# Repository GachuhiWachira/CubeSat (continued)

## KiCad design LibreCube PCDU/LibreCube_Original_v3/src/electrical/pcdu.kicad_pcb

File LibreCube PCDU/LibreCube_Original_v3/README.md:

# LibreCube / Platform / Power / Power Module

A basic Power Conditioning and Distribution Unit (PCDU) that
implements a full redundancy scheme and adheres to the LibreCube board
specification. The main features are:

- Input connectors for up to six solar cells (in configurations for up to 5 Volt)
- Conditioning of input power (linear energy transfer mode)
- Two Li-Ion batteries integrated on board
- Charge and discharge circuitry for batteries, depending on solar input and load
- Main power switch that disconnects all electrical loads from solar cell input and batteries
- Stable 5 Volt output power to attached loads
- Eight output switches for switchable loads

The user manual can be found [here](docs/manual/README.md).

## How to Build

See [here](docs/assembly/README.md) for instructions.

## How to Modify

The `src` folder contains the [KiCAD](https://www.kicad.org/) source files.

## Contribute

To learn more on how to successfully contribute please read the contributing
information in the [LibreCube Guidelines](https://librecube.gitlab.io/).

Want to get involved? Join us at [Matrix](https://app.element.io/#/room/#librecube.org:matrix.org)
or via [Email](mailto:info@librecube.org).

## License

The project is licensed under the CERN Open Hardware license.
See the [LICENSE](./LICENSE.txt) file for details.

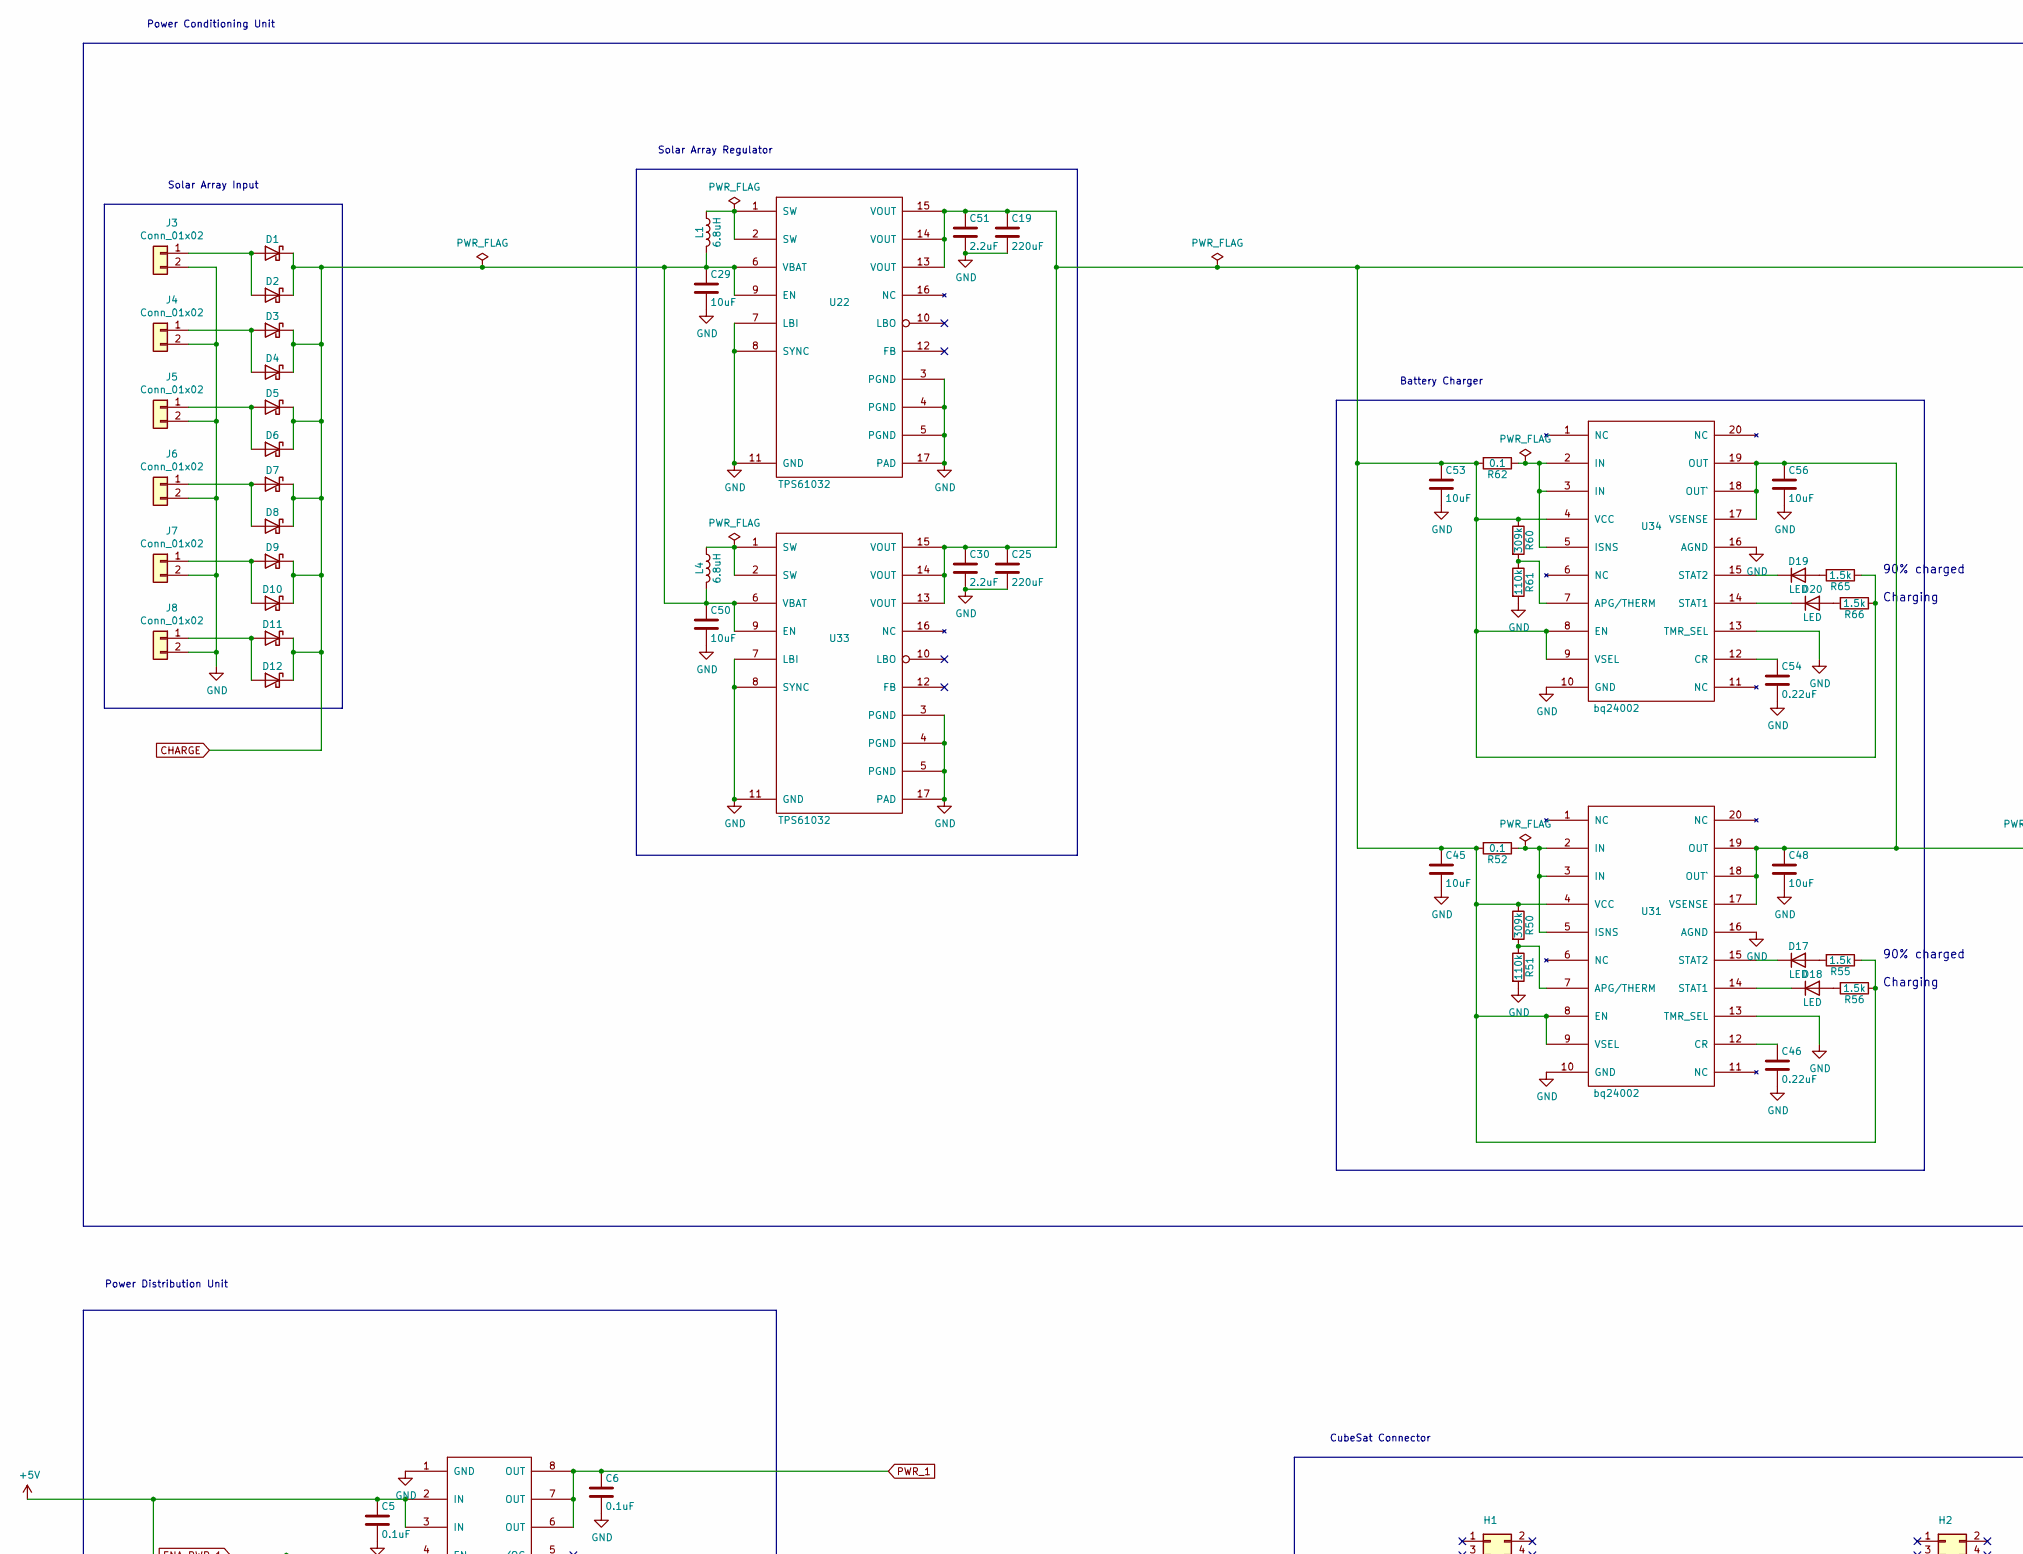
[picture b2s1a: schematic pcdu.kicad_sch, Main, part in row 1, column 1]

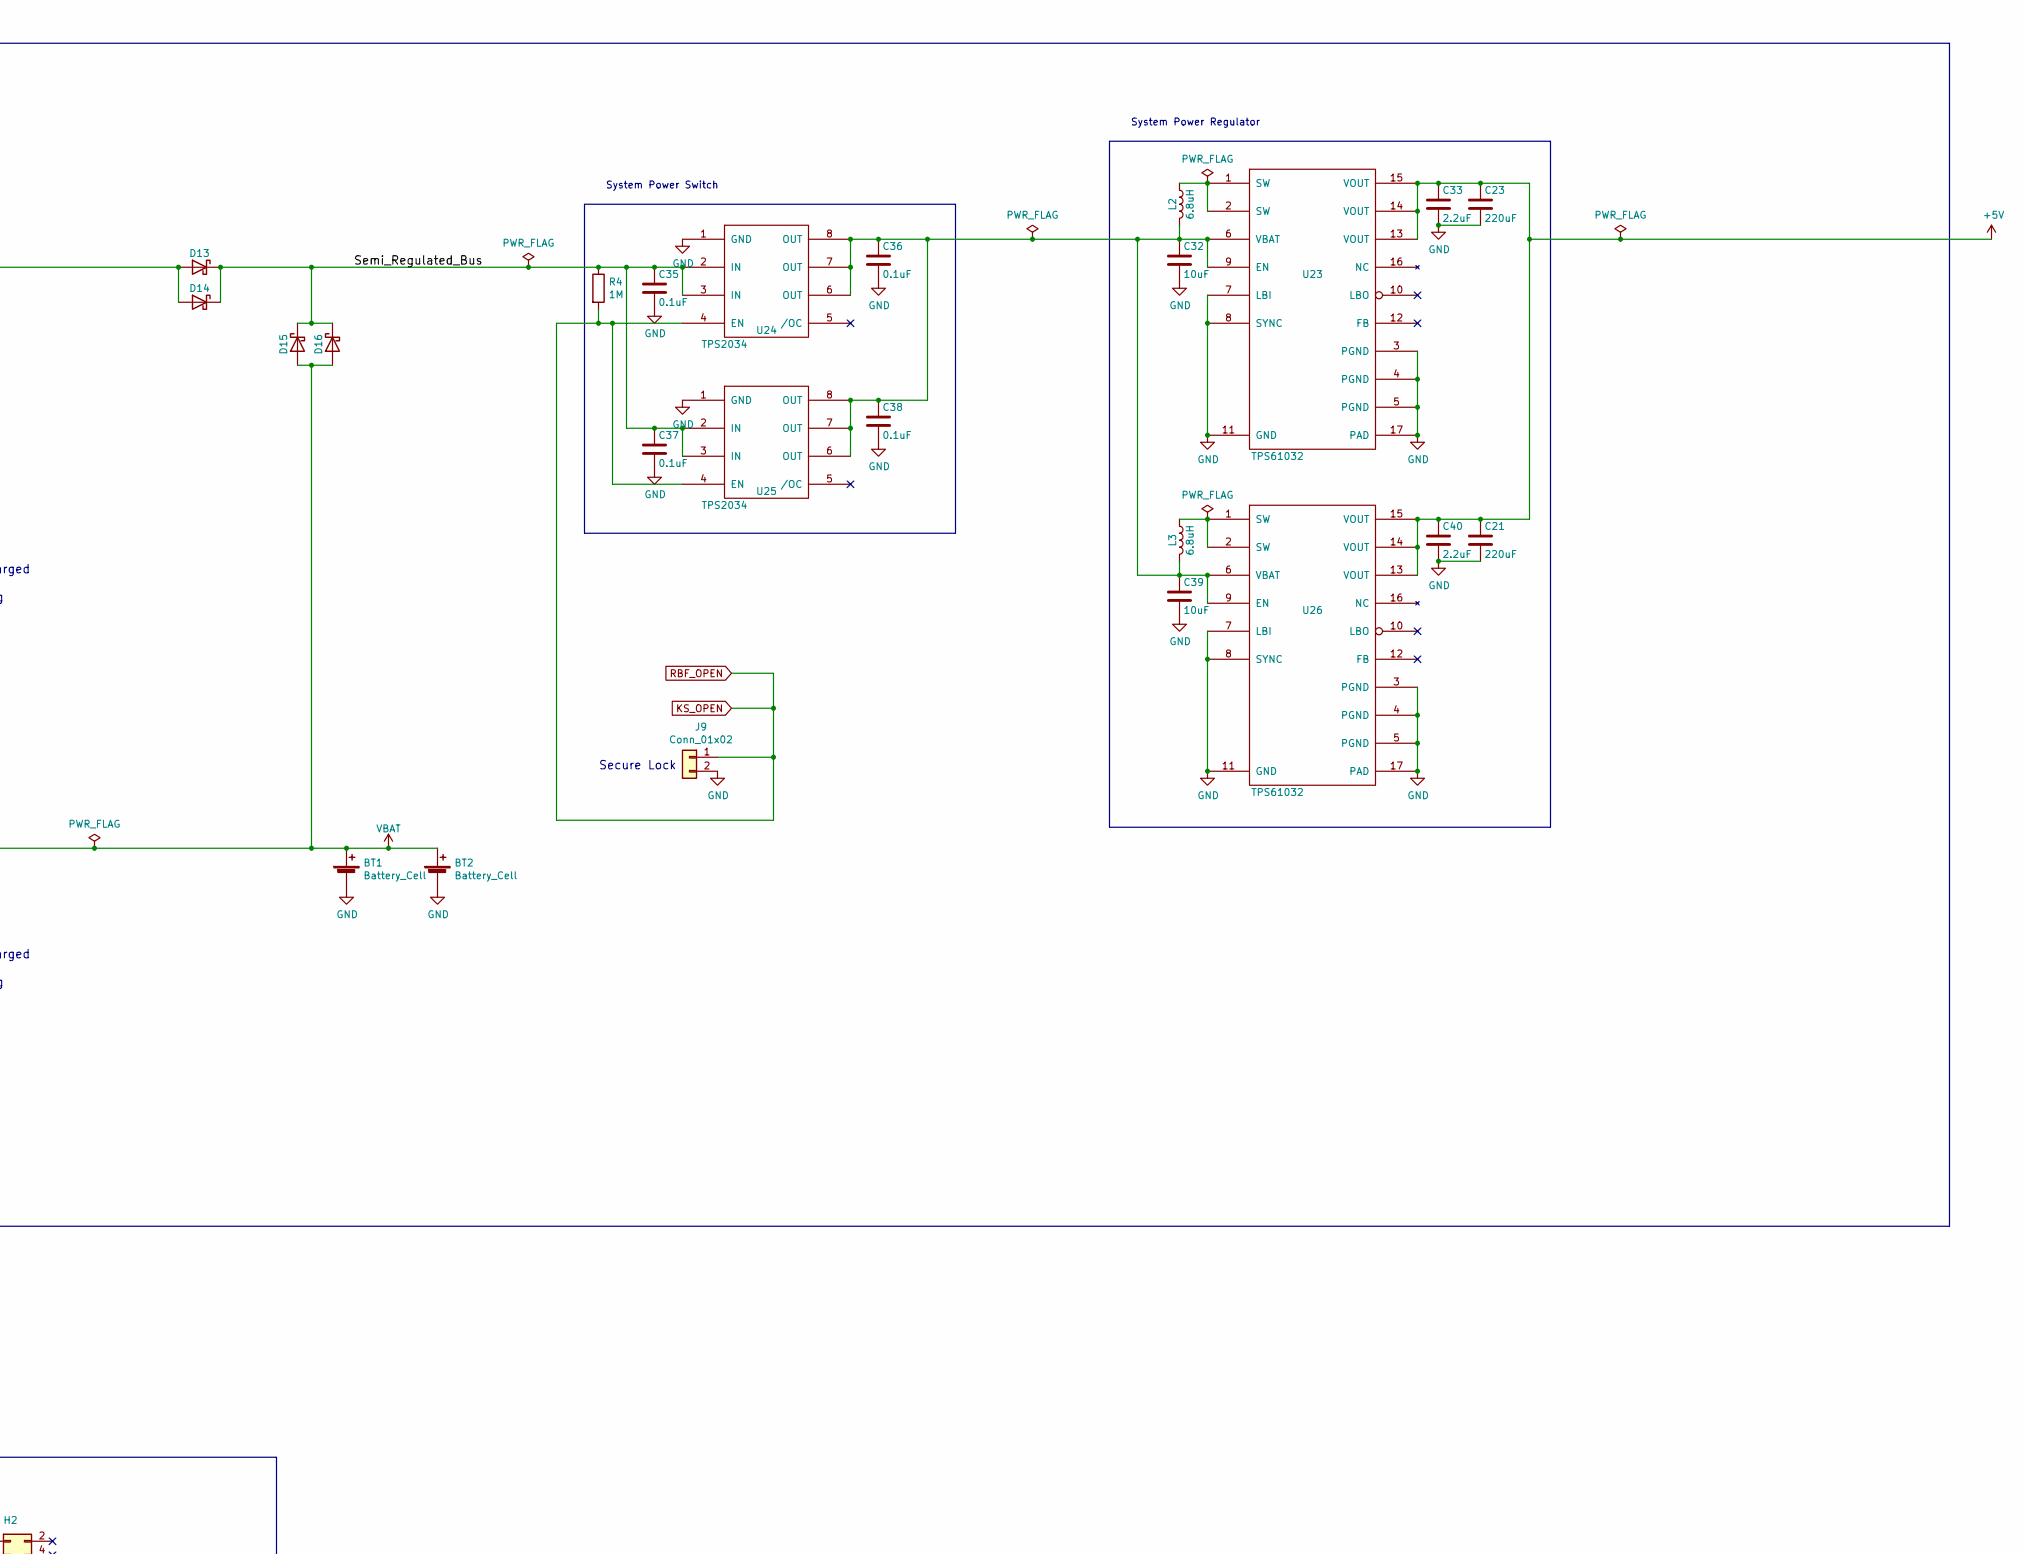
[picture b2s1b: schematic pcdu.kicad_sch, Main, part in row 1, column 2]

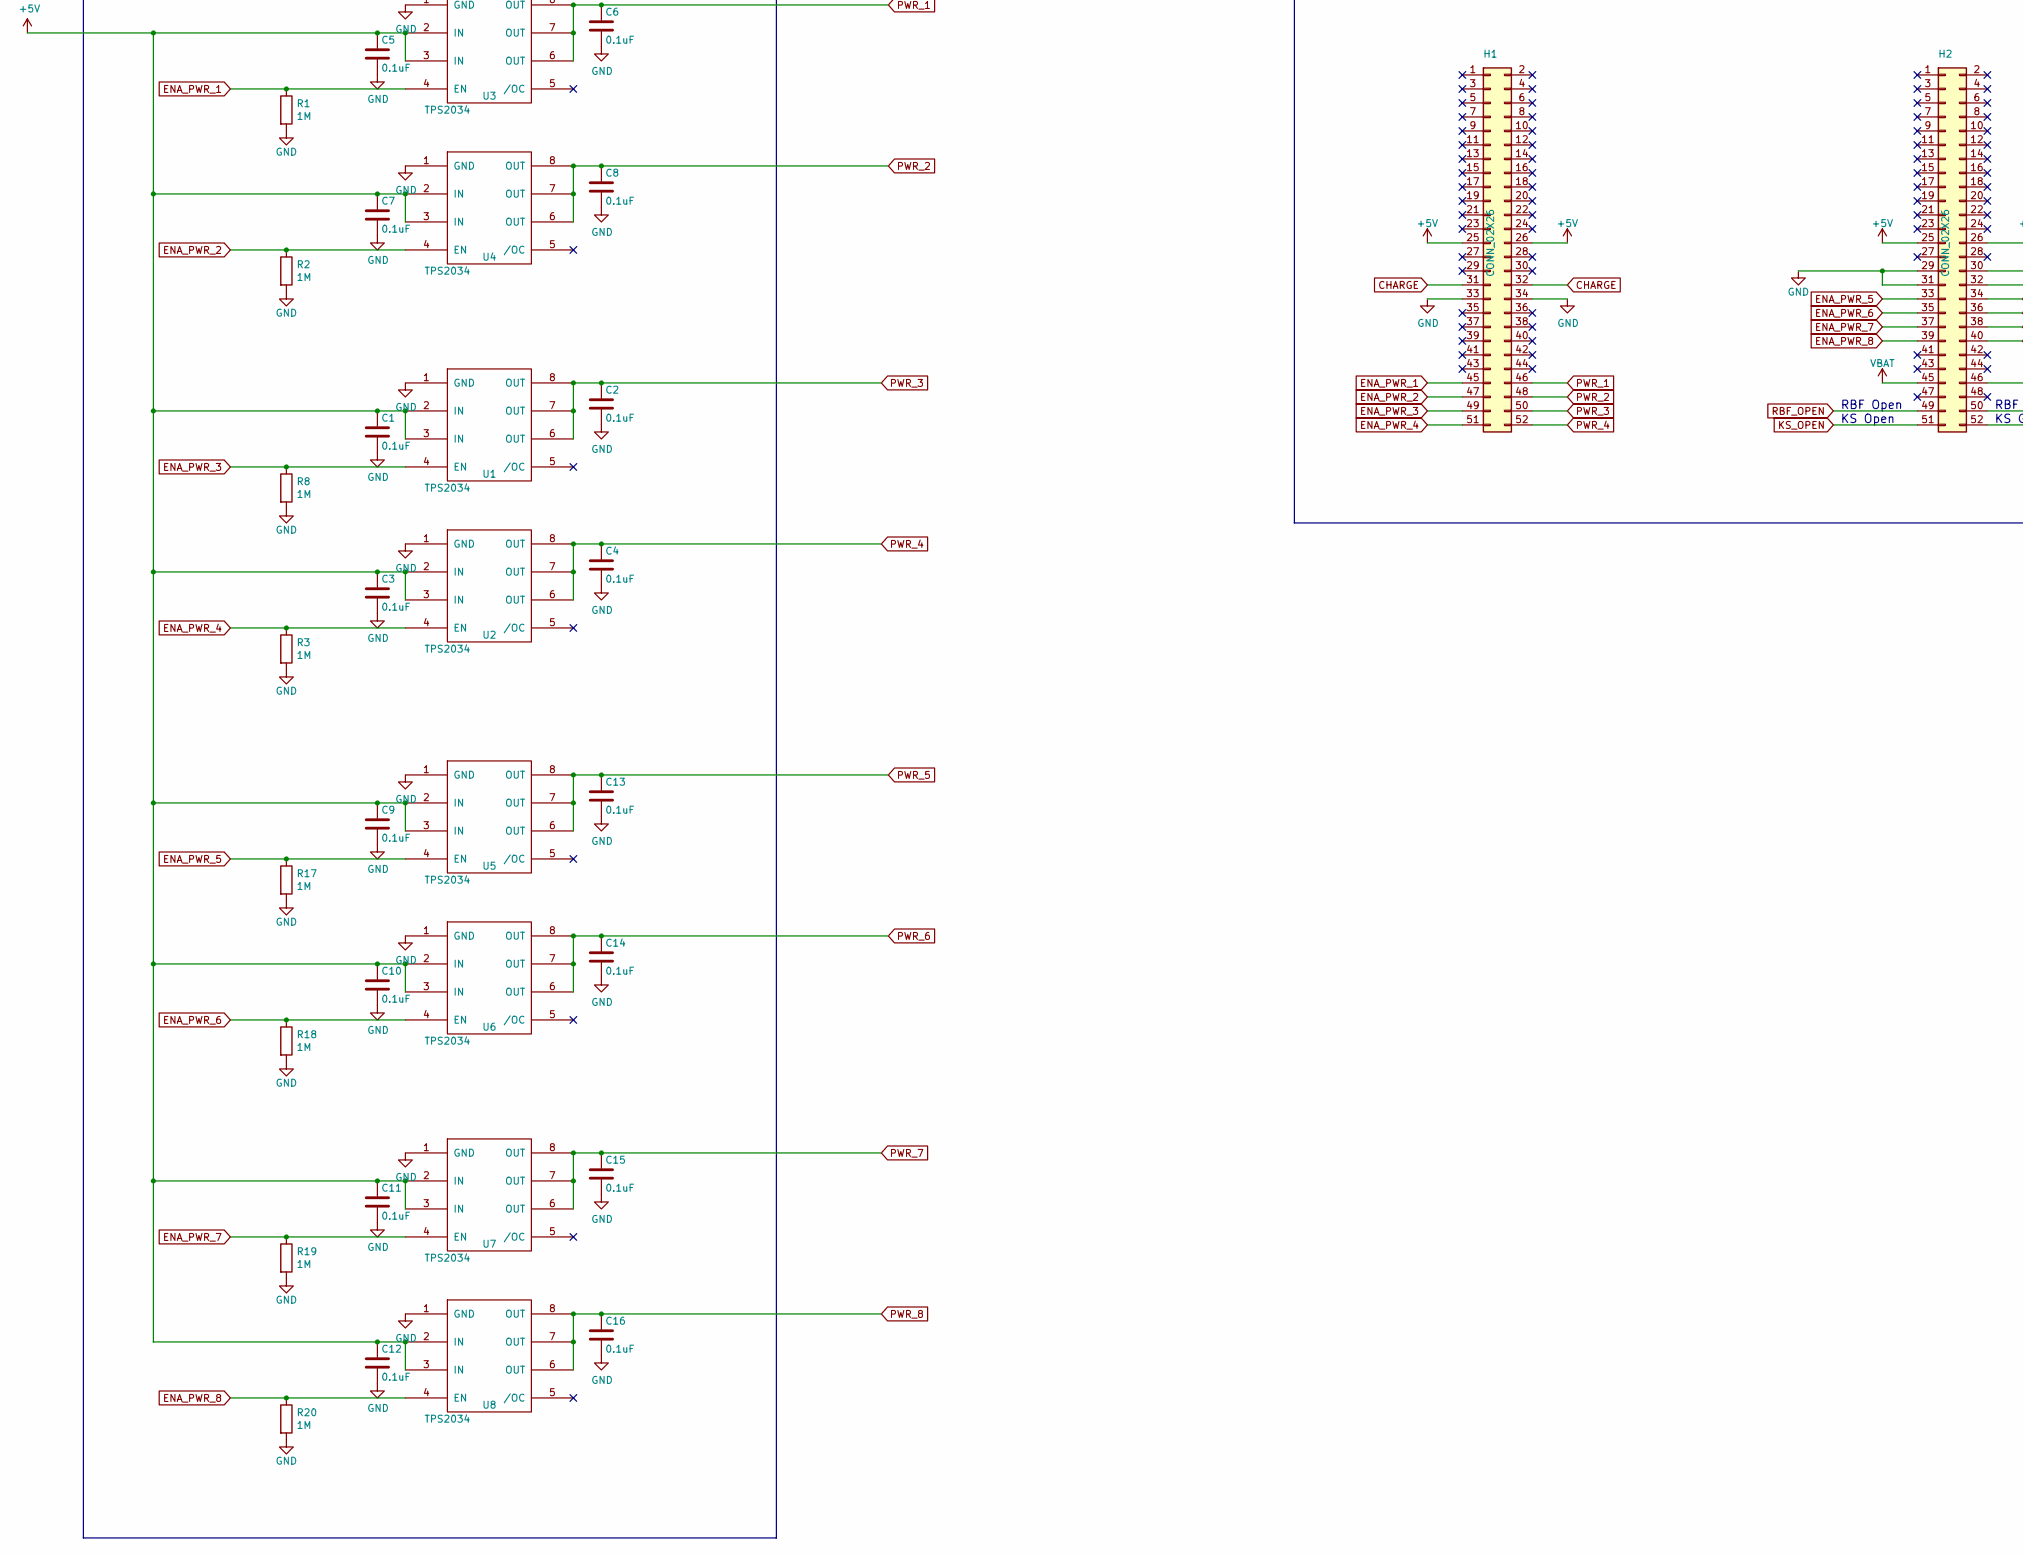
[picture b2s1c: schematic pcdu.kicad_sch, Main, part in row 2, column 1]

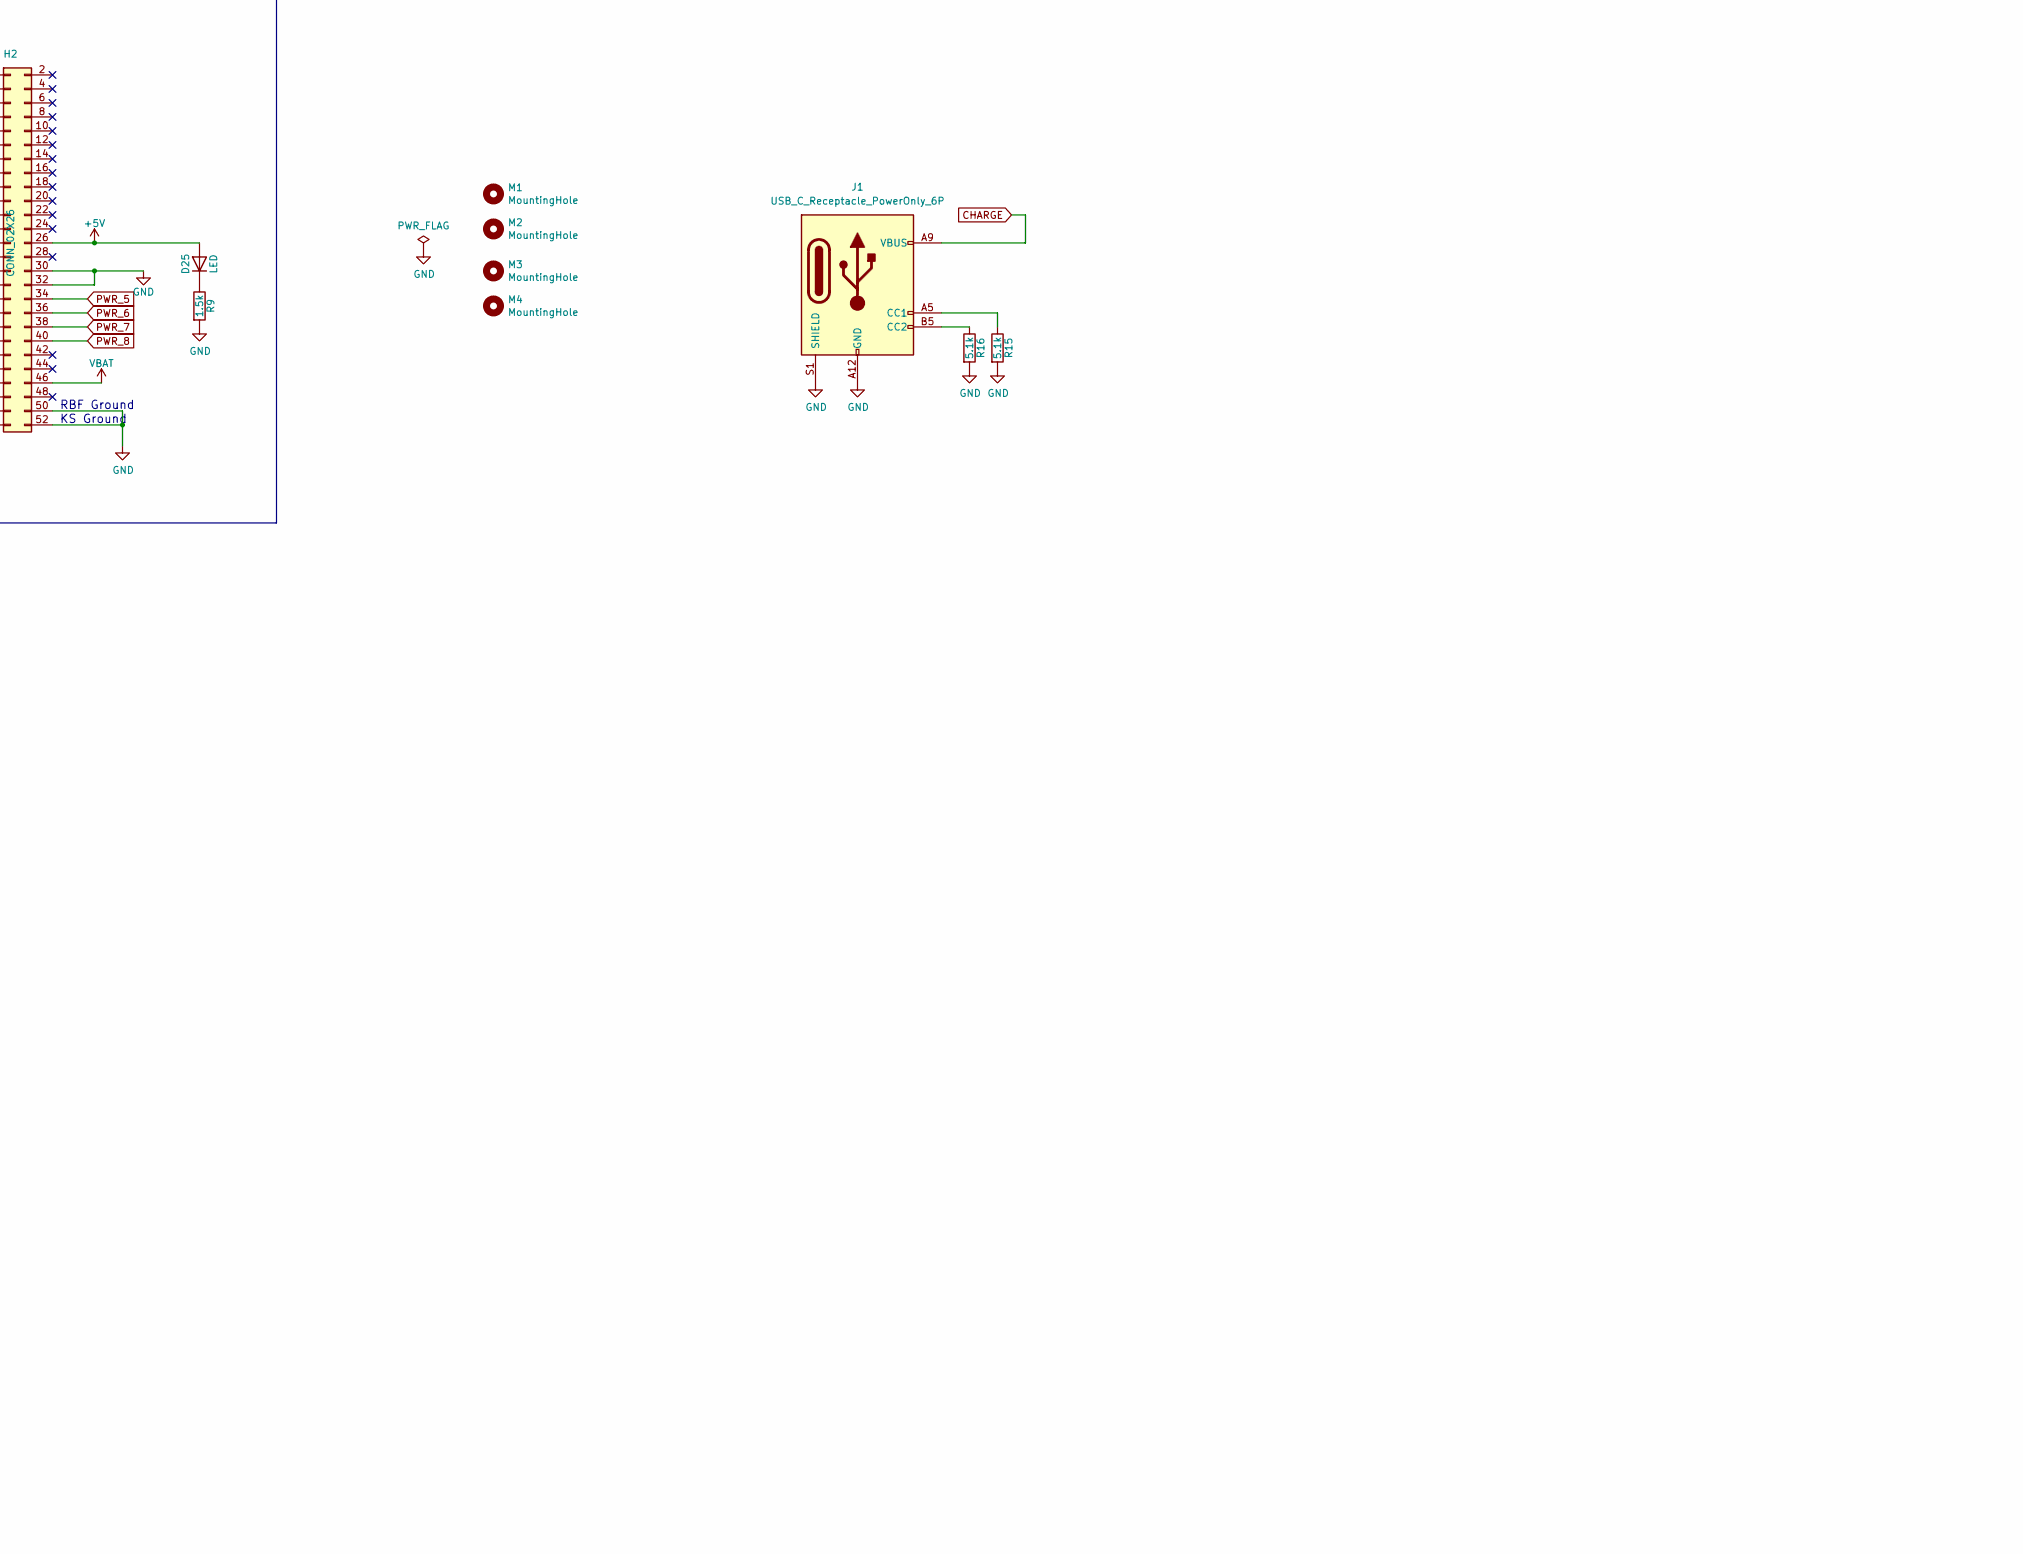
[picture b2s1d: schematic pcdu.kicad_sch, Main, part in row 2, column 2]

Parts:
BT1, BT2: Battery_Cell; BatteryHolder_Keystone_1042_1x18650
C1, C2, C3, C4, C5, C6, C7, C8, C9, C10, C11, C12, C13, C14, C15, C16, C35, C36, C37, C38: 0.1uF; C_0805_2012Metric
C19, C21, C23, C25: 220uF; CP_EIA-7343-31_Kemet-D
C29, C32, C39, C45, C48, C50, C53, C56: 10uF; C_0805_2012Metric
C30, C33, C40, C51: 2.2uF; C_0805_2012Metric
C46, C54: 0.22uF; C_0805_2012Metric
D1, D2, D3, D4, D5, D6, D7, D8, D9, D10, D11, D12, D13, D14, D15, D16: D_Schottky; D_SOD-123
D17, D18, D19, D20, D25: LED; D_0805_2012Metric
H1, H2: CONN_02X26; ESQ-126-39-x-D
J1: USB_C_Receptacle_PowerOnly_6P; USB_C_Receptacle_GCT_USB4125-xx-x-0190_6P_TopMnt_Horizontal
J3, J4, J5, J6, J7, J8: Conn_01x02; PinHeader_1x02_P2.54mm_Horizontal
J9: Conn_01x02; PinHeader_1x02_P2.54mm_Vertical
L1, L2, L3, L4: 6.8uH; L_10.4x10.4_H4.8
M1, M2, M3, M4: MountingHole; MountingHole_3.2mm_M3_Pad
R1, R2, R3, R4, R8, R17, R18, R19, R20: 1M; R_0805_2012Metric
R9, R55, R56, R65, R66: 1.5k; R_0805_2012Metric
R15, R16: 5.1k; R_0805_2012Metric
R50, R60: 309k; R_0805_2012Metric
R51, R61: 110k; R_0805_2012Metric
R52, R62: 0.1; R_1206_3216Metric
U1, U2, U3, U4, U5, U6, U7, U8, U24, U25: TPS2034; SO-8_3.9x4.9mm_P1.27mm
U22, U23, U26, U33: TPS61032; HTSSOP-16-1EP_4.4x5mm_P0.65mm_EP3x3mm
U31, U34: bq24002; HTSSOP-20-1EP_4.4x6.5mm_P0.65mm_EP2.85x4mm

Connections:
+5V: C1.1, C3.1, C5.1, C7.1, C9.1, C10.1, C11.1, C12.1, C21.1, C23.1, C33.1, C40.1, D25.2 (A), H1.25, H1.26, H2.25, H2.26, U1.2 (IN), U1.3 (IN), U2.2 (IN), U2.3 (IN), U3.2 (IN), U3.3 (IN), U4.2 (IN), U4.3 (IN), U5.2 (IN), U5.3 (IN), U6.2 (IN), U6.3 (IN), U7.2 (IN), U7.3 (IN), U8.2 (IN), U8.3 (IN), U23.13 (VOUT), U23.14 (VOUT), U23.15 (VOUT), U26.13 (VOUT), U26.14 (VOUT), U26.15 (VOUT)
/Semi_Regulated_Bus: C35.1, C37.1, D13.1 (K), D14.1 (K), D15.1 (K), D16.1 (K), R4.1, U24.2 (IN), U24.3 (IN), U25.2 (IN), U25.3 (IN)
CHARGE: C29.1, C50.1, D1.1 (K), D2.1 (K), D3.1 (K), D4.1 (K), D5.1 (K), D6.1 (K), D7.1 (K), D8.1 (K), D9.1 (K), D10.1 (K), D11.1 (K), D12.1 (K), H1.31, H1.32, J1.A9 (VBUS), J1.B9 (VBUS), L1.2, L4.2, U22.6 (VBAT), U22.9 (EN), U33.6 (VBAT), U33.9 (EN)
ENA_PWR_1: H1.45, R1.1, U3.4 (EN)
ENA_PWR_2: H1.47, R2.1, U4.4 (EN)
ENA_PWR_3: H1.49, R8.1, U1.4 (EN)
ENA_PWR_4: H1.51, R3.1, U2.4 (EN)
ENA_PWR_5: H2.33, R17.1, U5.4 (EN)
ENA_PWR_6: H2.35, R18.1, U6.4 (EN)
ENA_PWR_7: H2.37, R19.1, U7.4 (EN)
ENA_PWR_8: H2.39, R20.1, U8.4 (EN)
GND: BT1.2 (-), BT2.2 (-), C1.2, C2.2, C3.2, C4.2, C5.2, C6.2, C7.2, C8.2, C9.2, C10.2, C11.2, C12.2, C13.2, C14.2, C15.2, C16.2, C19.2, C21.2, C23.2, C25.2, C29.2, C30.2, C32.2, C33.2, C35.2, C36.2, C37.2, C38.2, C39.2, C40.2, C45.2, C46.2, C48.2, C50.2, C51.2, C53.2, C54.2, C56.2, H1.33, H1.34, H2.29, H2.30, H2.31, H2.32, H2.50, H2.52, J1.A12 (GND), J1.B12 (GND), J1.S1 (SHIELD), J3.2, J4.2, J5.2, J6.2, J7.2, J8.2, J9.2, R1.2, R2.2, R3.2, R8.2, R9.2, R15.2, R16.2, R17.2, R18.2, R19.2, R20.2, R51.2, R61.2, U1.1 (GND), U2.1 (GND), U3.1 (GND), U4.1 (GND), U5.1 (GND), U6.1 (GND), U7.1 (GND), U8.1 (GND), U22.3 (PGND), U22.4 (PGND), U22.5 (PGND), U22.7 (LBI), U22.8 (SYNC), U22.11 (GND), U22.17 (PAD), U23.3 (PGND), U23.4 (PGND), U23.5 (PGND), U23.7 (LBI), U23.8 (SYNC), U23.11 (GND), U23.17 (PAD), U24.1 (GND), U25.1 (GND), U26.3 (PGND), U26.4 (PGND), U26.5 (PGND), U26.7 (LBI), U26.8 (SYNC), U26.11 (GND), U26.17 (PAD), U31.10 (GND), U31.13 (TMR_SEL), U31.16 (AGND), U33.3 (PGND), U33.4 (PGND), U33.5 (PGND), U33.7 (LBI), U33.8 (SYNC), U33.11 (GND), U33.17 (PAD), U34.10 (GND), U34.13 (TMR_SEL), U34.16 (AGND)
KS_OPEN: H2.49, H2.51, J9.1, R4.2, U24.4 (EN), U25.4 (EN)
unnamed: D1.2 (A), D2.2 (A), J3.1
unnamed: D3.2 (A), D4.2 (A), J4.1
unnamed: D5.2 (A), D6.2 (A), J5.1
unnamed: D7.2 (A), D8.2 (A), J6.1
unnamed: D9.2 (A), D10.2 (A), J7.1
unnamed: D11.2 (A), D12.2 (A), J8.1
unnamed: C19.1, C25.1, C30.1, C45.1, C51.1, C53.1, D13.2 (A), D14.2 (A), R50.1, R52.2, R55.1, R56.1, R60.1, R62.2, R65.1, R66.1, U22.13 (VOUT), U22.14 (VOUT), U22.15 (VOUT), U31.4 (VCC), U31.8 (EN), U31.9 (VSEL), U33.13 (VOUT), U33.14 (VOUT), U33.15 (VOUT), U34.4 (VCC), U34.8 (EN), U34.9 (VSEL)
unnamed: D17.2 (A), R55.2
unnamed: D17.1 (K), U31.15 (STAT2)
unnamed: D18.2 (A), R56.2
unnamed: D18.1 (K), U31.14 (STAT1)
unnamed: D19.2 (A), R65.2
unnamed: D19.1 (K), U34.15 (STAT2)
unnamed: D20.2 (A), R66.2
unnamed: D20.1 (K), U34.14 (STAT1)
unnamed: D25.1 (K), R9.1
unnamed: J1.A5 (CC1), R15.1
unnamed: J1.B5 (CC2), R16.1
unnamed: L1.1, U22.1 (SW), U22.2 (SW)
unnamed: L2.1, U23.1 (SW), U23.2 (SW)
unnamed: L3.1, U26.1 (SW), U26.2 (SW)
unnamed: L4.1, U33.1 (SW), U33.2 (SW)
unnamed: C32.1, C36.1, C38.1, C39.1, L2.2, L3.2, U23.6 (VBAT), U23.9 (EN), U24.6 (OUT), U24.7 (OUT), U24.8 (OUT), U25.6 (OUT), U25.7 (OUT), U25.8 (OUT), U26.6 (VBAT), U26.9 (EN)
unnamed: R50.2, R51.1, U31.7 (APG/THERM)
unnamed: C46.1, U31.12 (CR)
unnamed: R52.1, U31.2 (IN), U31.3 (IN), U31.5 (ISNS)
unnamed: R60.2, R61.1, U34.7 (APG/THERM)
unnamed: C54.1, U34.12 (CR)
unnamed: R62.1, U34.2 (IN), U34.3 (IN), U34.5 (ISNS)
PWR_1: C6.1, H1.46, U3.6 (OUT), U3.7 (OUT), U3.8 (OUT)
PWR_2: C8.1, H1.48, U4.6 (OUT), U4.7 (OUT), U4.8 (OUT)
PWR_3: C2.1, H1.50, U1.6 (OUT), U1.7 (OUT), U1.8 (OUT)
PWR_4: C4.1, H1.52, U2.6 (OUT), U2.7 (OUT), U2.8 (OUT)
PWR_5: C13.1, H2.34, U5.6 (OUT), U5.7 (OUT), U5.8 (OUT)
PWR_6: C14.1, H2.36, U6.6 (OUT), U6.7 (OUT), U6.8 (OUT)
PWR_7: C15.1, H2.38, U7.6 (OUT), U7.7 (OUT), U7.8 (OUT)
PWR_8: C16.1, H2.40, U8.6 (OUT), U8.7 (OUT), U8.8 (OUT)
VBAT: BT1.1 (+), BT2.1 (+), C48.1, C56.1, D15.2 (A), D16.2 (A), H2.45, H2.46, U31.17 (VSENSE), U31.18 (OUT`), U31.19 (OUT), U34.17 (VSENSE), U34.18 (OUT`), U34.19 (OUT)

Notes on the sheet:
Solar Array Input
90% charged
RBF Ground
KS Open
RBF Open
CubeSat Connector
KS Ground
Solar Array Regulator
Charging
System Power Switch
Power Distribution Unit
Power Conditioning Unit
System Power Regulator
Secure Lock
Battery Charger

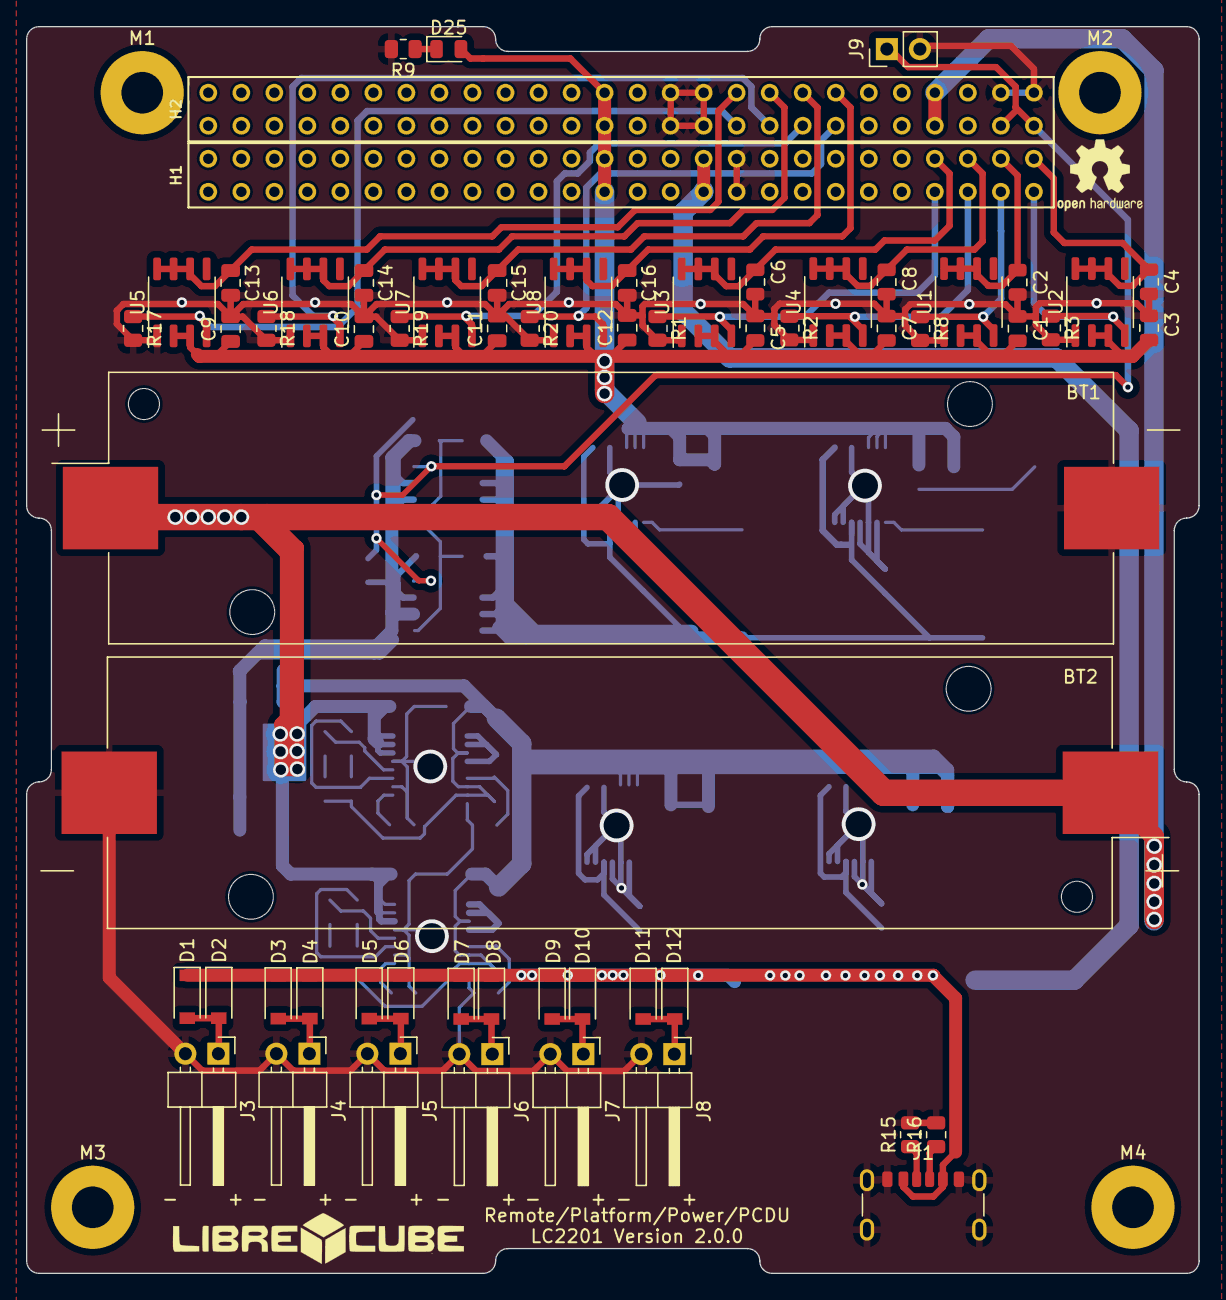
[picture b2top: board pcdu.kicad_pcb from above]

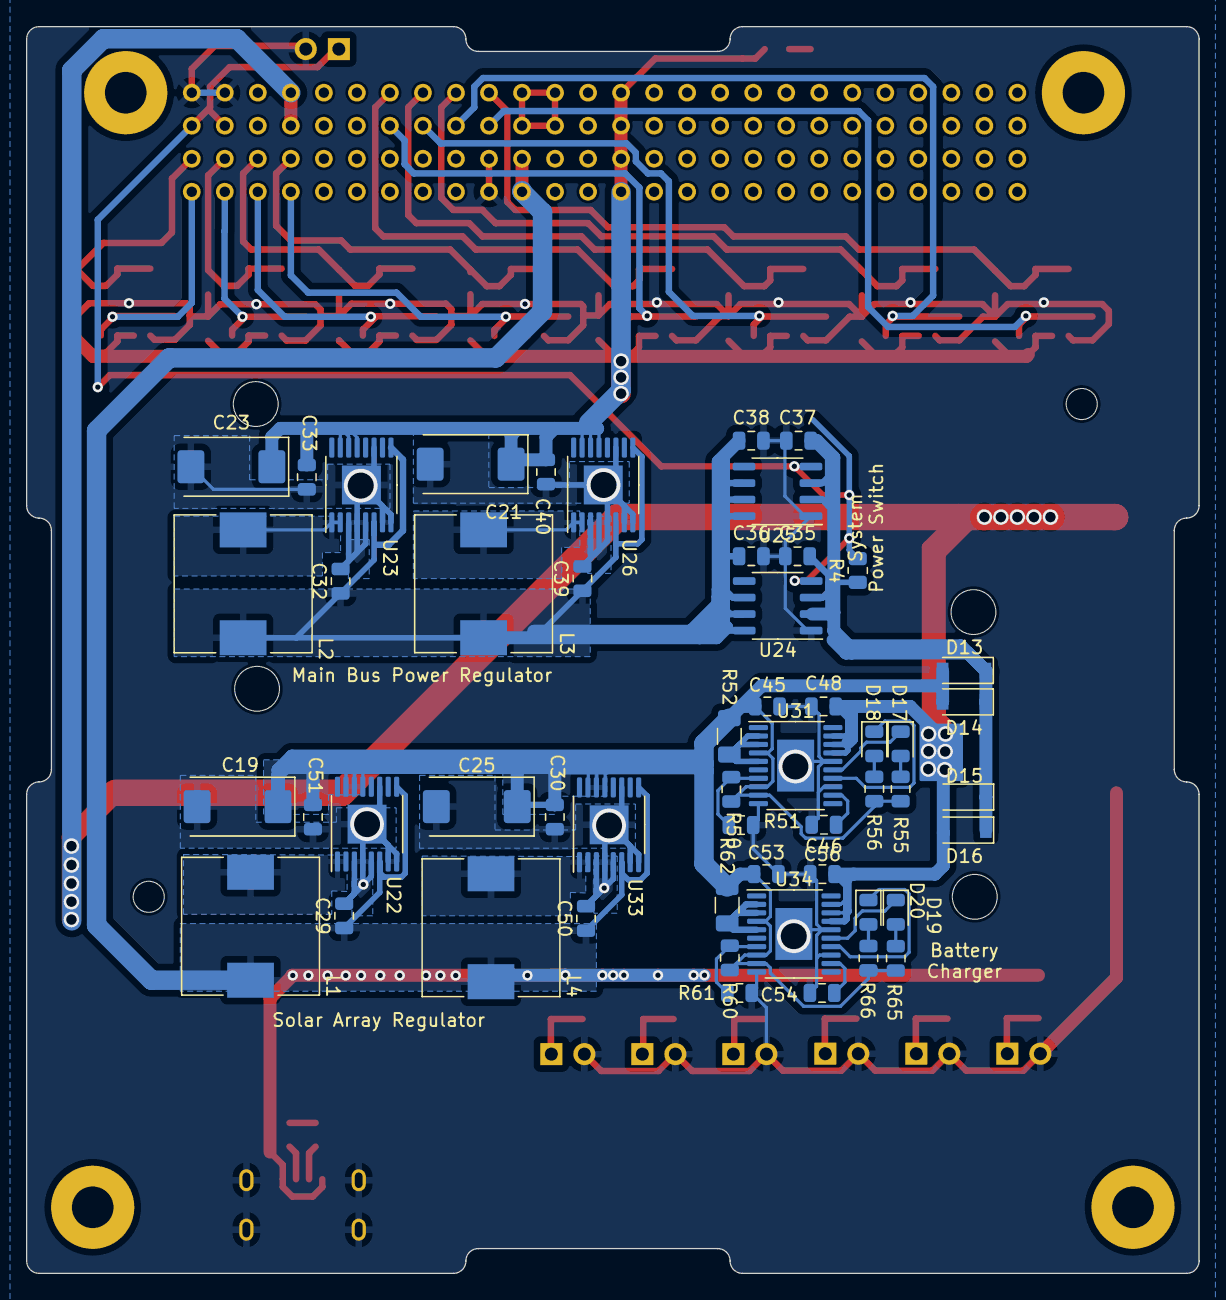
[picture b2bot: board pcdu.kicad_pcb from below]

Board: 2 copper layers, 90.2 x 95.9 mm, 117 parts (53 on the bottom side), 51 nets.

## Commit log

2024-08-06 Uploaded PCDU files
2024-08-06 Renamed the folders
2024-08-06 Included "My version"
2024-08-06 Added PCB file
2024-08-06 renaming
2024-08-06 Starting over
2024-08-06 new project
2024-08-06 removing repetition
2024-08-06 More updates
2024-09-19 Uploaded PCDUv2
2024-09-19 Updated Kicad Version
2024-09-20 Uploaded latest version from LibreCube
2024-09-29 New components
2024-10-01 PCDU updates
2024-10-03 PCB Layout
2024-10-08 EPS Routing
2025-06-20 PCDU finished
2025-06-23 PCDU Complete
